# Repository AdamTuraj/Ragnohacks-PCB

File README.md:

# Ragnohacks PCB

This is the repo containing the design files for the PCB which may be used in the [Ragnohacks hackathon](https://ragnohacks.ca)

## 3D PCB Preview
.png)
.png)

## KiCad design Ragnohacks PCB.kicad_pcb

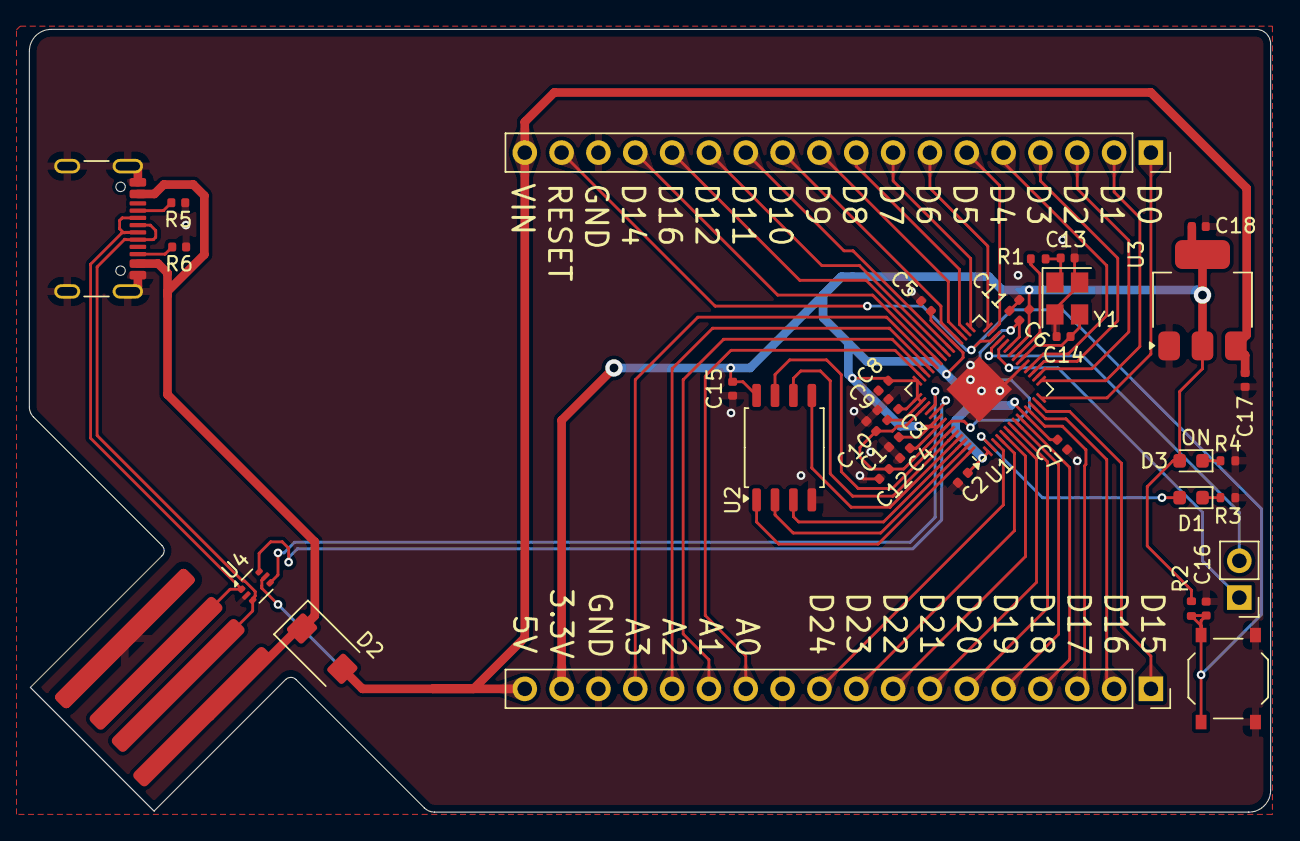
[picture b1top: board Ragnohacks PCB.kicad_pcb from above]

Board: 2 copper layers, 85.6 x 54.0 mm, 38 parts (0 on the bottom side), 55 nets.

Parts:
C1, C2, C3, C4, C5, C6, C7, C8, C11, C12, C15, C16, C17: 0.1uF; C_0402_1005Metric
C9, C10: 1uF; C_0402_1005Metric
C13, C14: 18pF; C_0402_1005Metric
C18: 10uF; C_0402_1005Metric
D1, D3: LED; LED_0603_1608Metric
D2: D_Schottky; D_SMA
J1: Conn_01x02; PinHeader_1x02_P2.54mm_Vertical
J2, J3: Conn_01x18; PinSocket_1x18_P2.54mm_Vertical
J4: USB_A; USB_A_Edge
J5: USB_C_Receptacle_USB2.0_16P; USB_C_Receptacle_GCT_USB4105-xx-A_16P_TopMnt_Horizontal
R1: 1k; R_0402_1005Metric
R2: 10k; R_0402_1005Metric
R3, R4: 360R; R_0402_1005Metric
R5, R6: 5k1; C_0402_1005Metric
SW1: SW_Push; SW_Push_1P1T_XKB_TS-1187A
U1: RP2040; QFN-56-1EP_7x7mm_P0.4mm_EP3.2x3.2mm
U2: W25Q128JVS; SOIC-8_5.23x5.23mm_P1.27mm
U3: LD1117S33TR_SOT223; SOT-223-3_TabPin2
U4: USBLC6-2P6; SOT-666
Y1: 12MHz; Crystal_SMD_3225-4Pin_3.2x2.5mm

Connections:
+1V1: C10.1, C11.1, C12.1, U1.23 (DVDD), U1.45 (VREG_VOUT), U1.50 (DVDD)
+3V3: C1.1, C2.1, C3.1, C4.1, C5.1, C6.1, C7.1, C8.1, C9.1, C15.1, C18.1, D3.2 (A), J3.17, R2.2, U1.1 (IOVDD), U1.10 (IOVDD), U1.22 (IOVDD), U1.33 (IOVDD), U1.42 (IOVDD), U1.43 (ADC_AVDD), U1.44 (VREG_IN), U1.48 (USB_VDD), U1.49 (IOVDD), U2.8 (VCC), U3.2 (VO)
+5V: C17.1, D2.1 (K), J2.18, J3.18, U3.3 (VI), U4.5 (VBUS)
A0: J3.12, U1.41 (GPIO29_ADC3)
A1: J3.13, U1.40 (GPIO28_ADC2)
A2: J3.14, U1.39 (GPIO27_ADC1)
A3: J3.15, U1.38 (GPIO26_ADC0)
D0: J2.1, U1.14 (GPIO11)
D1: J2.2, U1.15 (GPIO12)
D2: J2.3, U1.16 (GPIO13)
D3: J2.4, U1.17 (GPIO14)
D4: J2.5, U1.18 (GPIO15)
D5: J2.6, U1.27 (GPIO16)
D6: J2.7, U1.28 (GPIO17)
D7: J2.8, U1.29 (GPIO18)
D8: J2.9, U1.30 (GPIO19)
D9: J2.10, U1.31 (GPIO20)
D10: J2.11, U1.32 (GPIO21)
D11: J2.12, U1.34 (GPIO22)
D12: J2.13, U1.35 (GPIO23)
D13: J2.14, U1.36 (GPIO24)
D14: J2.15, U1.37 (GPIO25)
D15: J3.1, U1.13 (GPIO10)
D16: J3.2, U1.12 (GPIO9)
D17: J3.3, U1.11 (GPIO8)
D18: J3.4, U1.9 (GPIO7)
D19: J3.5, U1.8 (GPIO6)
D20: J3.6, U1.7 (GPIO5)
D21: J3.7, U1.6 (GPIO4)
D22: J3.8, U1.5 (GPIO3)
D23: J3.9, U1.4 (GPIO2)
D24: J3.10, U1.3 (GPIO1)
DN: J4.3 (D+), J5.A7 (D-), J5.B7 (D-), U4.1 (I/O1)
DP: J4.2 (D-), J5.A6 (D+), J5.B6 (D+), U4.3 (I/O2)
FLASH_CLK: U1.52 (QSPI_SCLK), U2.6 (CLK)
FLASH_CS: U1.56 (QSPI_SS), U2.1 (~CS)
FLASH_SD0: U1.53 (QSPI_SD0), U2.5 (DI(IO0))
FLASH_SD1: U1.55 (QSPI_SD1), U2.2 (DO(IO1))
FLASH_SD2: U1.54 (QSPI_SD2), U2.3 (IO2)
FLASH_SD3: U1.51 (QSPI_SD3), U2.7 (IO3)
GND: C1.2, C2.2, C3.2, C4.2, C5.2, C6.2, C7.2, C8.2, C9.2, C10.2, C11.2, C12.2, C13.1, C14.1, C15.2, C16.1, C17.2, C18.2, J2.16, J3.11, J3.16, J4.4 (GND), J4.5 (Shield), J5.A1 (GND), J5.A12 (GND), J5.B1 (GND), J5.B12 (GND), J5.S1 (SHIELD), R3.2, R4.2, R5.1, R6.1, SW1.1, U1.19 (TESTEN), U1.57 (GND), U2.4 (GND), U3.1 (GND), U4.2 (GND), Y1.2, Y1.4
LED_25: D1.2 (A), U1.2 (GPIO0)
unnamed: C13.2, R1.1, Y1.1
unnamed: D1.1 (K), R3.1
unnamed: D2.2 (A), J4.1 (VBUS), J5.A4 (VBUS), J5.A9 (VBUS), J5.B4 (VBUS), J5.B9 (VBUS)
unnamed: D3.1 (K), R4.1
unnamed: J1.1, U1.24 (SWCLK)
unnamed: J1.2, U1.25 (SWD)
unnamed: J5.A5 (CC1), R5.2
unnamed: J5.B5 (CC2), R6.2
unnamed: C14.2, U1.20 (XIN), Y1.3
unnamed: R1.2, U1.21 (XOUT)
RESET: C16.2, J2.17, R2.1, SW1.2, U1.26 (RUN)
USB_DN: U1.46 (USB_DM), U4.4 (I/O2)
USB_DP: U1.47 (USB_DP), U4.6 (I/O1)

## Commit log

2024-08-29 Finish schematic
2024-08-29 Finish schematic and part choosing, get initial quote
2024-08-29 Start layout, add PCBWay parts
2024-08-29 Start tracing
2024-08-29 Finish tracing pins
2024-08-29 Finish tracing
2024-08-29 The finishing touches
2024-08-29 Add README
2024-08-31 Change USB port, adjust header position, start tracing
2024-09-02 Rev 2 of the Ragnohacks PCB
2024-09-02 Move USB port, routing adjustments
2025-01-24 Swap USB pins
2026-03-10 Replace PCB preview images with updated links
    Updated image links for 3D PCB previews in README.
